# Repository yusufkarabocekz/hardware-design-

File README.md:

# Hardware Libraries Workspace

Bu repository, çeşitli donanım projeleri ve kütüphanelerini içeren kapsamlı bir workspace'tir. Endüstriyel sensör modülleri, güç yönetimi çözümleri, drone kontrolcüleri ve eğitim projeleri gibi farklı alanlarda geliştirilmiş projeleri barındırır.

## 📁 Proje Kategorileri

### 🔧 Endüstriyel Sensör Modülleri
- **Endüstriyel Sensör Modülü** - Endüstriyel uygulamalar için geliştirilmiş sensör modülü

- **UKB_Ballica** - UKB (Uçuş Kontrol Bilgisayarı) Sistemi

### ⚡ Güç Yönetimi Çözümleri
- **Güç Dağıtım Kartı** - Çoklu güç dağıtımı için tasarlanmış PCB

- **LM2596 Buck Converter** - Step-down (düşürücü) DC-DC dönüştürücü modülü

- **XL6009 Boost Converter** - Step-up (yükseltici) DC-DC dönüştürücü modülü

### 🚁 Drone ve Uçuş Kontrolcüleri
- **flight-controller-for-dronmarket-main** - Drone market için özel uçuş kontrolcüsü

- **speedybeef4v4_clone** - SpeedyBee F4 V4 uçuş kontrolcüsü klonu

### 📊 IMU ve Sensör Sürücüleri
- **STM32-ICM42688-P** - ICM-42688-P IMU sensörü için STM32 sürücüsü

- **stm32f103_bmi088** - BMI-088 IMU sensörü için STM32F103 sürücüsü

### 🎓 Eğitim Projeleri
- **xBowtie Eğitim** - xBowtie platformu - Mustafa Berk Aydoğan - PCB Tasarım - Bir Elektronik Kartın Yaşam Döngüsü

## 🚀 Özellikler

- **Modüler Tasarım**: Her proje bağımsız olarak geliştirilmiş ve kullanılabilir
- **Çoklu Platform Desteği**: STM32, Arduino ve diğer mikrodenetleyici platformları
- **Kapsamlı Dokümantasyon**: Her proje için detaylı README dosyaları
- **Örnek Kodlar**: Pratik kullanım için hazırlanmış örnekler
- **Endüstriyel Standartlar**: Profesyonel geliştirme standartlarına uygun

## 📋 Proje Listesi

| Proje Adı | Kategori | Açıklama |
|-----------|----------|----------|
| Endüstriyel Sensör Modülü | Endüstriyel | Endüstriyel uygulamalar için sensör modülü |
| UKB_Ballica | Endüstriyel | Ultrasonik kuvvet basınç sensörü |
| Güç Dağıtım Kartı | Güç Yönetimi | Çoklu güç dağıtım PCB'si |
| LM2596 Buck Converter | Güç Yönetimi | Step-down DC-DC dönüştürücü |
| XL6009 Boost Converter | Güç Yönetimi | Step-up DC-DC dönüştürücü |
| STM32-ICM42688-P | IMU/Sensör | ICM-42688-P STM32 sürücüsü |
| stm32f103_bmi088 | IMU/Sensör | BMI-088 STM32F103 sürücüsü |
| flight-controller-for-dronmarket-main | Drone | Drone market uçuş kontrolcüsü |
| speedybeef4v4_clone | Drone | SpeedyBee F4 V4 klonu |
| xBowtie Eğitim | Eğitim | xBowtie eğitim materyalleri |

## 🛠️ Teknolojiler

- **Mikrodenetleyiciler**: STM32F103, STM32F4, Arduino
- **Sensörler**: BMI-088, ICM-42688-P, MPU9250, GPS M8N, MS5611 etc. 
- **İletişim Protokolleri**: I2C, SPI, UART, RS232/485
- **PCB Tasarım**: KiCad
- **Programlama**: C, C++, Arduino, STM32
- **Güç Yönetimi**: LM2596, XL6009

## 🤝 Katkıda Bulunma

1. Bu repository'yi fork edin
2. Yeni bir branch oluşturun (`git checkout -b feature/yeni-ozellik`)
3. Değişikliklerinizi commit edin (`git commit -am 'Yeni özellik eklendi'`)
4. Branch'inizi push edin (`git push origin feature/yeni-ozellik`)
5. Pull Request oluşturun

## 📄 Lisans

Bu projeler açık kaynak olarak geliştirilmiştir. Her proje kendi lisans bilgilerini içerir.

## 📞 İletişim

Projeler hakkında sorularınız için:
- GitHub Issues kullanabilirsiniz

---

**Not**: Bu workspace sürekli güncellenmektedir. Yeni projeler ve güncellemeler için repository'yi takip etmeyi unutmayın.

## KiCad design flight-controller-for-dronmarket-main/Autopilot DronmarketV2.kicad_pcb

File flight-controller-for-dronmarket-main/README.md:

# flight-controller-for-dronmarket

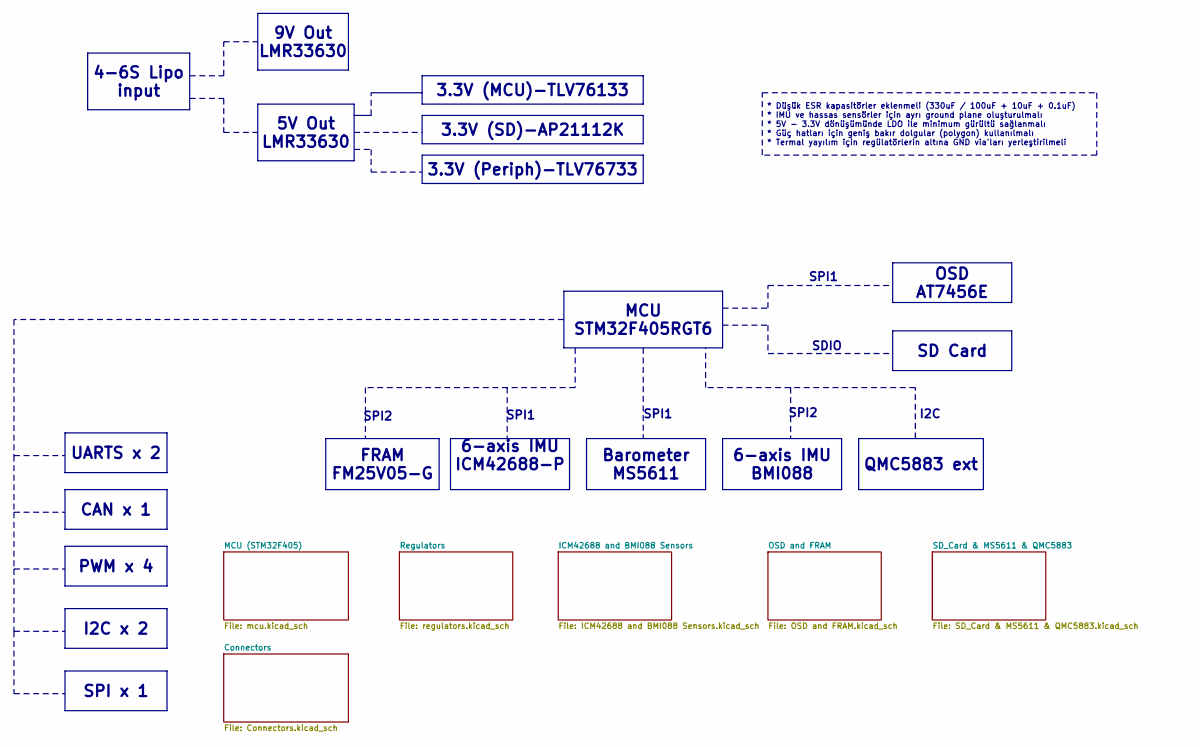
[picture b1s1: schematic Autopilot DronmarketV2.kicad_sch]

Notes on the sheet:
SDIO
SPI1
SPI1
I2C
SPI2
QMC5883 ext
6-axis IMU BMI088
I2C x 2
FRAM FM25V05-G
SD Card
3.3V (MCU)-TLV76133
6-axis IMU ICM42688-P
Barometer MS5611
3.3V (Periph)-TLV76733
4-6S Lipo input
5V Out LMR33630
SPI x 1
MCU STM32F405RGT6
PWM x 4
UARTS x 2
9V Out LMR33630
OSD AT7456E
3.3V (SD)-AP21112K
CAN x 1
* Düşük ESR kapasitörler eklenmeli (330uF / 100uF + 10uF + 0.1uF) * IMU ve hassas sensörler için ayrı ground plane oluşturulmalı * 5V - 3.3V dönüşümünde LDO ile minimum gürültü sağlanmalı * Güç hatları için geniş bakır dolgular (polygon) kullanılmalı * Termal yayılım için regülatörlerin altına GND 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

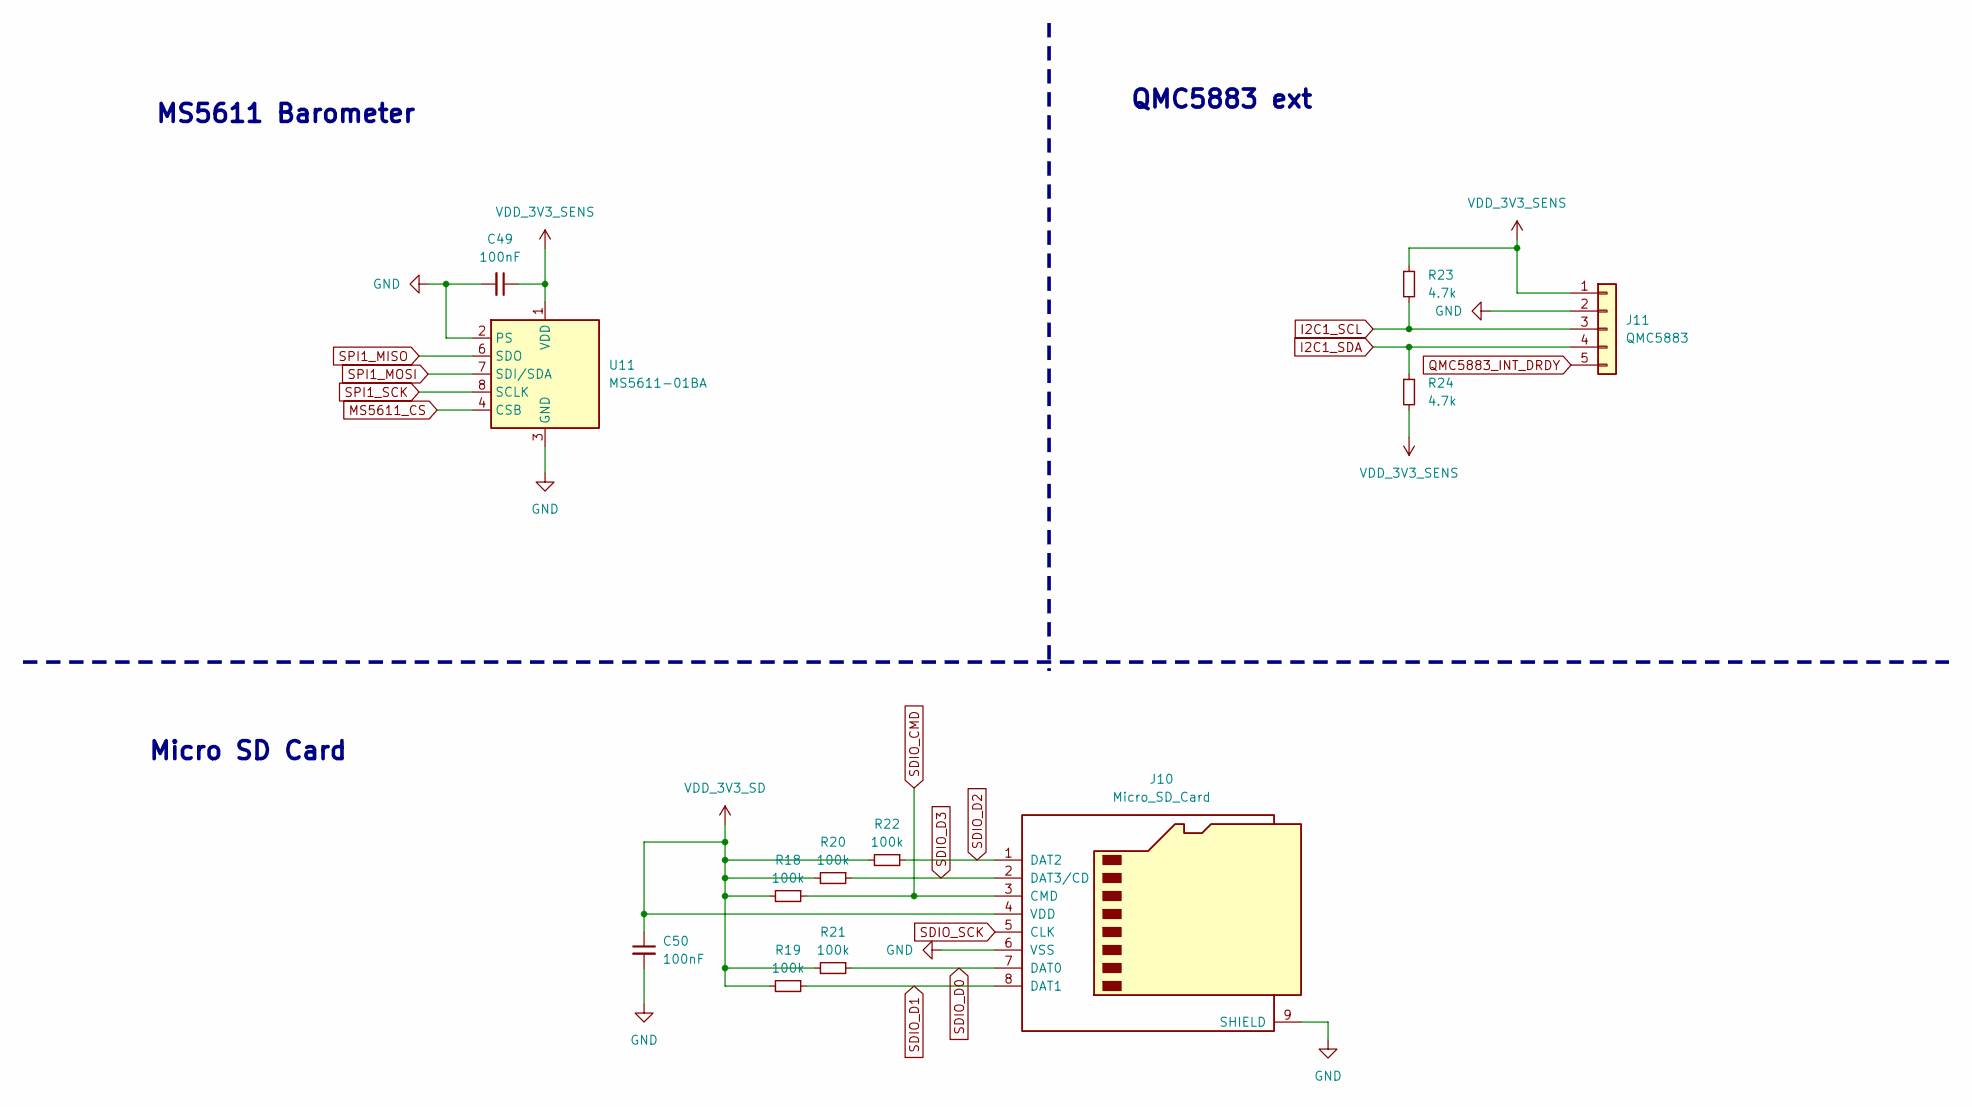
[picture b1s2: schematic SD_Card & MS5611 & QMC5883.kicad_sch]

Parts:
C49, C50: 100nF; C_0402_1005Metric
J10: Micro_SD_Card; MOLEX_503398-1892
J11: QMC5883; JST_GH_SM05B-GHS-TB_1x05-1MP_P1.25mm_Horizontal
R18, R19, R20, R21, R22: 100k; R_0402_1005Metric
R23, R24: 4.7k; R_0402_1005Metric
U11: MS5611-01BA; LGA-8_3x5mm_P1.25mm

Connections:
GND: C49.2, C50.2, J10.6 (VSS), J10.9 (SHIELD), J11.2, J11.MP, U11.2 (PS), U11.3 (GND); also elsewhere on the board
I2C1_SCL: J11.3, R23.2; also elsewhere on the board
I2C1_SDA: J11.4, R24.1; also elsewhere on the board
MS5611_CS: U11.4 (CSB), U11.5 (CSB); also elsewhere on the board
QMC5883_INT_DRDY: J11.5; also elsewhere on the board
SDIO_CMD: J10.3 (CMD), R18.1; also elsewhere on the board
SDIO_D0: J10.7 (DAT0), R21.1; also elsewhere on the board
SDIO_D1: J10.8 (DAT1), R19.1; also elsewhere on the board
SDIO_D2: J10.1 (DAT2), R22.1; also elsewhere on the board
SDIO_D3: J10.2 (DAT3/CD), R20.1; also elsewhere on the board
SDIO_SCK: J10.5 (CLK); also elsewhere on the board
SPI1_MISO: U11.6 (SDO); also elsewhere on the board
SPI1_MOSI: U11.7 (SDI/SDA); also elsewhere on the board
SPI1_SCK: U11.8 (SCLK); also elsewhere on the board
VDD_3V3_SD: C50.1, J10.4 (VDD), R18.2, R19.2, R20.2, R21.2, R22.2; also elsewhere on the board
VDD_3V3_SENS: C49.1, J11.1, R23.1, R24.2, U11.1 (VDD); also elsewhere on the board

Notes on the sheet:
QMC5883 ext
Micro SD Card
MS5611 Barometer

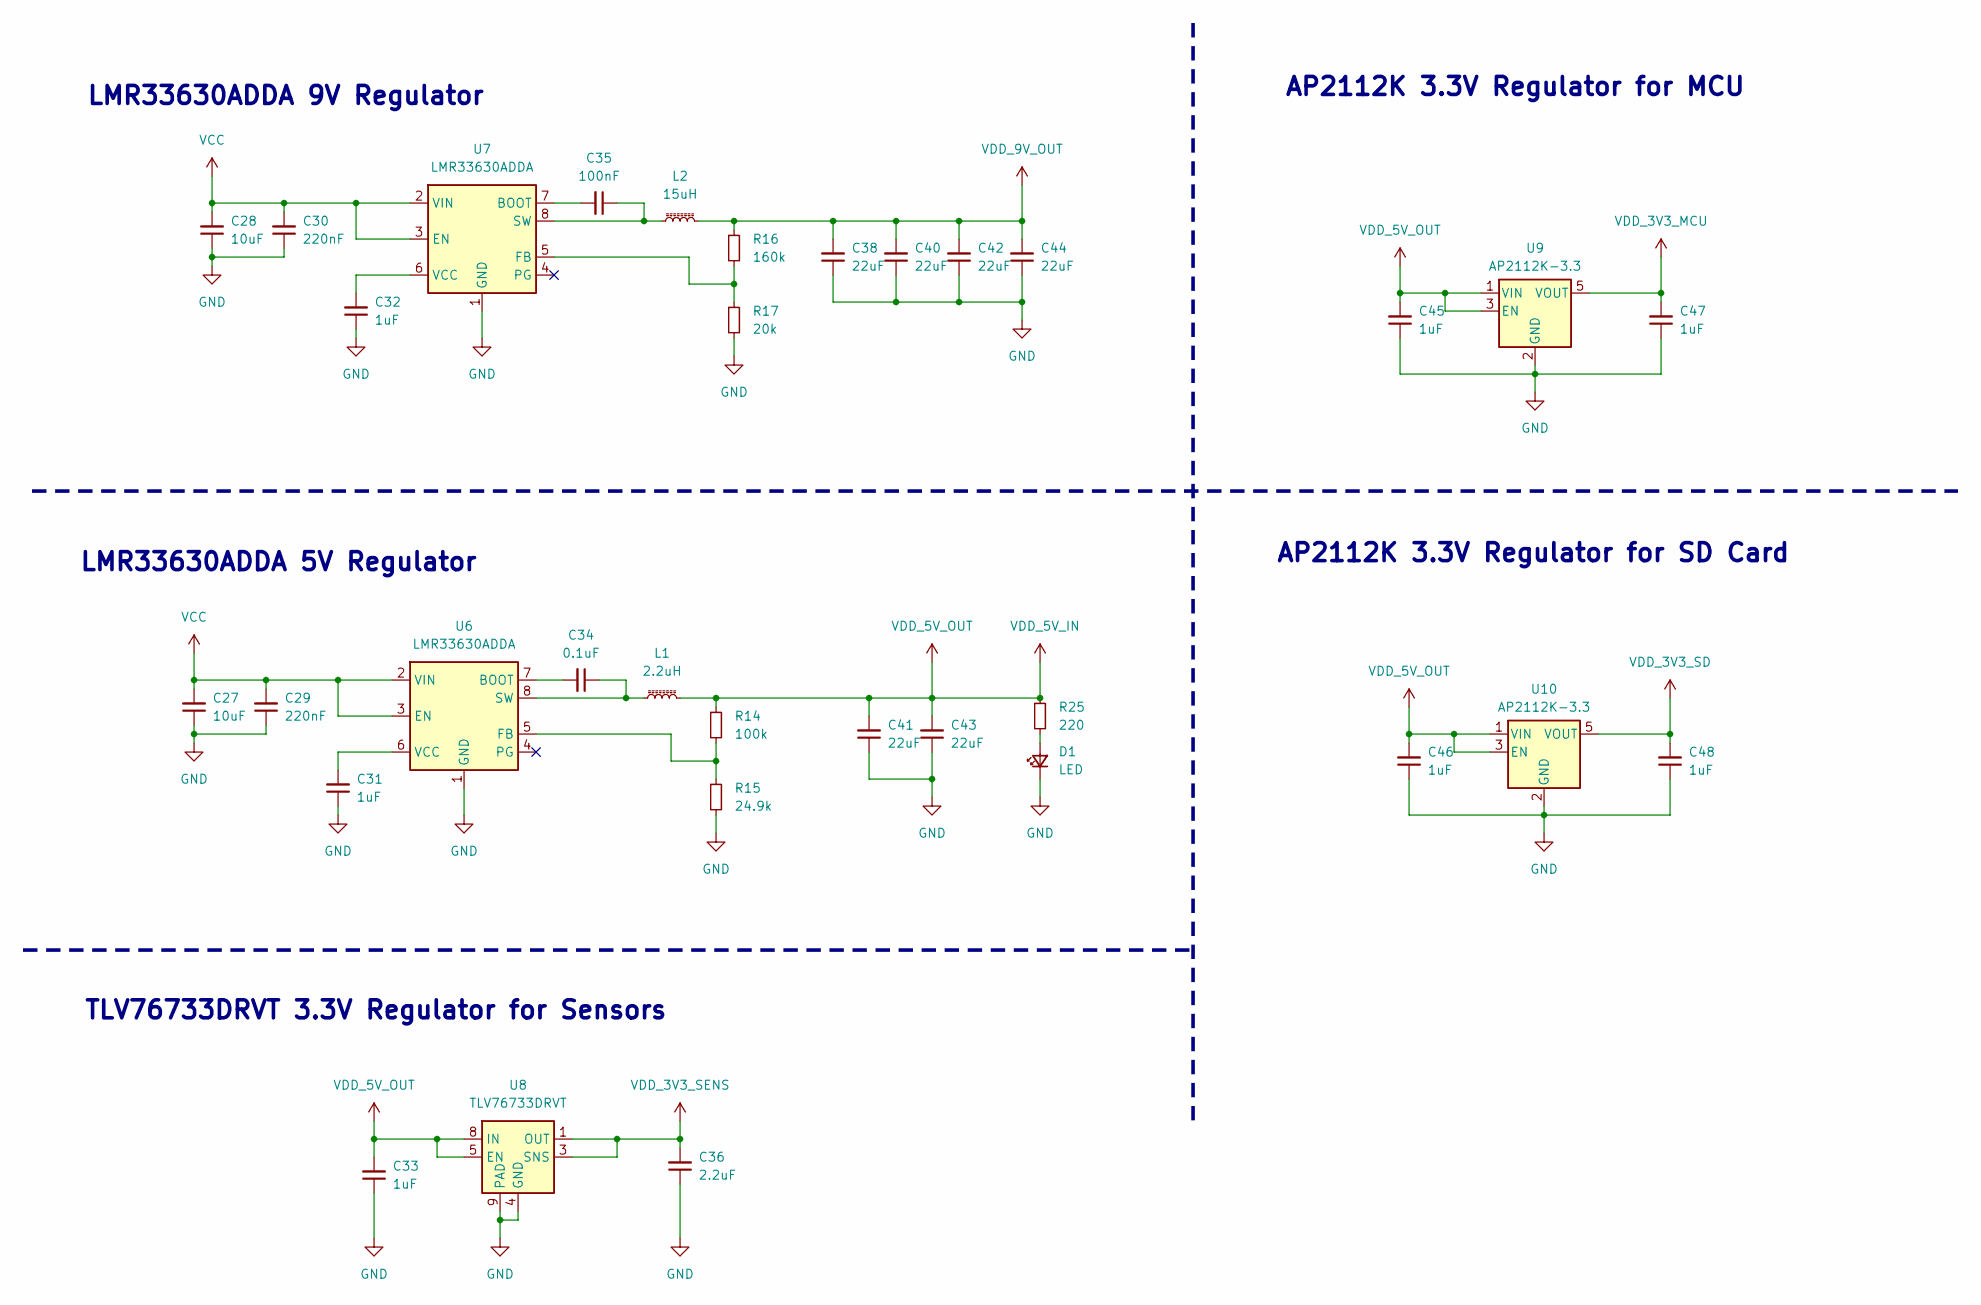
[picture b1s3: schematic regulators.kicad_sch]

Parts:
C27, C28: 10uF; C_0402_1005Metric
C29, C30: 220nF; C_0402_1005Metric
C31, C32, C33, C45, C46, C47, C48: 1uF; C_0402_1005Metric
C34: 0.1uF; C_0402_1005Metric
C35: 100nF; C_0402_1005Metric
C36: 2.2uF; C_0402_1005Metric
C38, C40, C41, C42, C43, C44: 22uF; C_0402_1005Metric
D1: LED; LED_0603_1608Metric
L1: 2.2uH; L_Chilisin_BMRB00060650
L2: 15uH; L_Chilisin_BMRB00060650
R14: 100k; R_0402_1005Metric
R15: 24.9k; R_0402_1005Metric
R16: 160k; R_0402_1005Metric
R17: 20k; R_0402_1005Metric
R25: 220; R_0402_1005Metric
U6, U7: LMR33630ADDA; Texas_HSOP-8-1EP_3.9x4.9mm_P1.27mm_ThermalVias
U8: TLV76733DRVT; SON65P200X200X80-7N
U9, U10: AP2112K-3.3; SOT-23-5

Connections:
GND: C27.1, C28.1, C29.1, C30.1, C31.1, C32.1, C33.1, C36.1, C38.1, C40.1, C41.1, C42.1, C43.1, C44.1, C45.1, C46.1, C47.1, C48.1, D1.1 (K), R15.2, R17.2, U6.1 (GND), U6.9 (GND), U7.1 (GND), U7.9 (GND), U8.4 (GND), U8.6 (GND), U8.9 (PAD), U9.2 (GND), U10.2 (GND); also elsewhere on the board
unnamed: D1.2 (A), R25.2
unnamed: C34.2, U6.7 (BOOT)
unnamed: R14.2, R15.1, U6.5 (FB)
unnamed: C34.1, L1.1, U6.8 (SW)
unnamed: C31.2, U6.6 (VCC)
unnamed: C35.2, U7.7 (BOOT)
unnamed: R16.2, R17.1, U7.5 (FB)
unnamed: C35.1, L2.1, U7.8 (SW)
unnamed: C32.2, U7.6 (VCC)
VCC: C27.2, C28.2, C29.2, C30.2, U6.2 (VIN), U6.3 (EN), U7.2 (VIN), U7.3 (EN); also elsewhere on the board
VDD_3V3_MCU: C47.2, U9.5 (VOUT); also elsewhere on the board
VDD_3V3_SD: C48.2, U10.5 (VOUT); also elsewhere on the board
VDD_3V3_SENS: C36.2, U8.1 (OUT), U8.3 (SNS); also elsewhere on the board
VDD_5V_IN: C33.2, C41.2, C43.2, C45.2, C46.2, L1.2, R14.1, R25.1, U8.5 (EN), U8.8 (IN), U9.1 (VIN), U9.3 (EN), U10.1 (VIN), U10.3 (EN); also elsewhere on the board
VDD_9V_OUT: C38.2, C40.2, C42.2, C44.2, L2.2, R16.1; also elsewhere on the board

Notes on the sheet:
TLV76733DRVT 3.3V Regulator for Sensors
AP2112K 3.3V Regulator for MCU
AP2112K 3.3V Regulator for SD Card
LMR33630ADDA 9V Regulator
LMR33630ADDA 5V Regulator

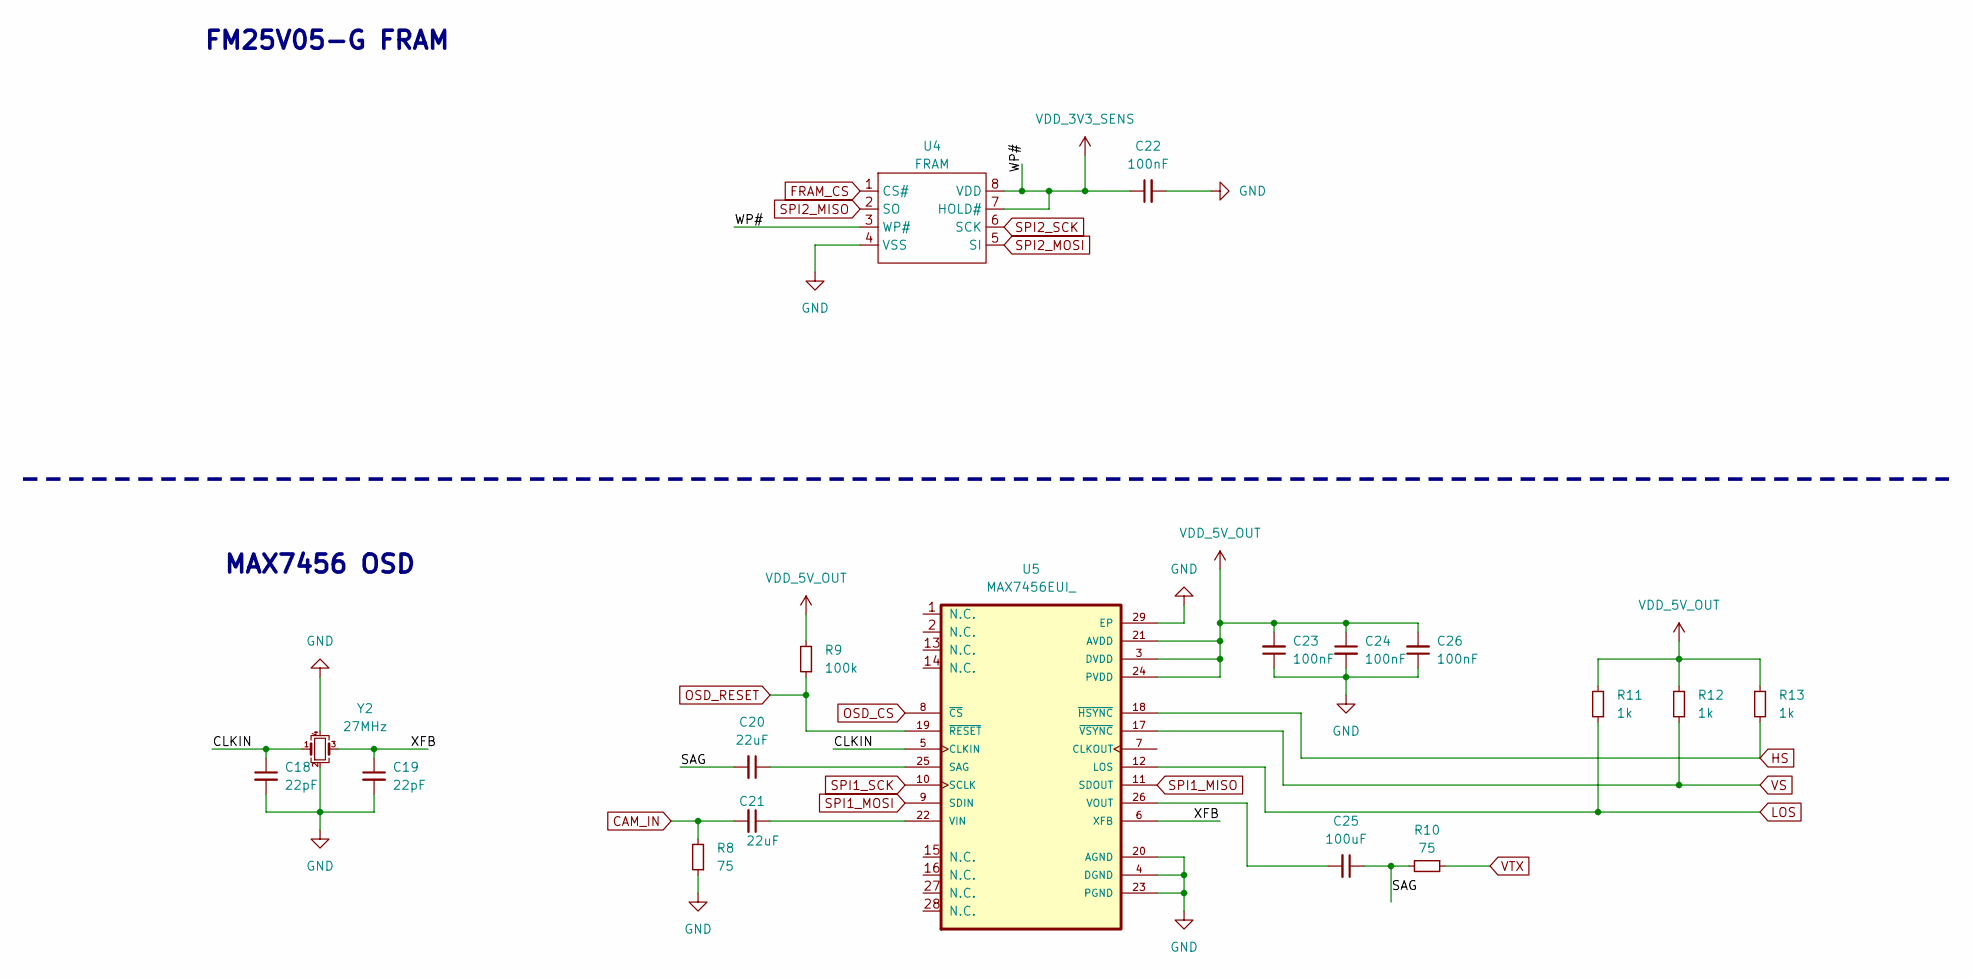
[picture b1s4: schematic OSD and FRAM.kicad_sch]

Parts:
C18, C19: 22pF; C_0402_1005Metric
C20: 22uF; C_0402_1005Metric
C21: 22uF; C_1210_3225Metric
C22, C23, C24, C26: 100nF; C_0402_1005Metric
C25: 100uF; C_1210_3225Metric
R8, R10: 75; R_0402_1005Metric
R9: 100k; R_0402_1005Metric
R11, R12, R13: 1k; R_0402_1005Metric
U4: FRAM; SOIC127P602X172-8N
U5: MAX7456EUI_; SOP65P637X110-28N
Y2: 27MHz; Crystal_SMD_SeikoEpson_FA238V-4Pin_3.2x2.5mm

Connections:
/OSD and FRAM/CLKIN: C18.1, U5.5 (CLKIN), Y2.1
/OSD and FRAM/SAG: C20.2, C25.1, R10.2
/OSD and FRAM/XFB: C19.1, U5.6 (XFB), Y2.3
CAM_IN: C21.2, R8.2; also elsewhere on the board
FRAM_CS: U4.1 (CS#); also elsewhere on the board
GND: C18.2, C19.2, C22.2, C23.1, C24.2, C26.1, R8.1, U4.4 (VSS), U5.4 (DGND), U5.20 (AGND), U5.23 (PGND), U5.29 (EP), Y2.2, Y2.4; also elsewhere on the board
HS: R13.2, U5.18 (~HSYNC)
LOS: R11.1, U5.12 (LOS)
unnamed: C20.1, U5.25 (SAG)
unnamed: C21.1, U5.22 (VIN)
unnamed: C25.2, U5.26 (VOUT)
OSD_CS: U5.8 (~CS); also elsewhere on the board
OSD_RESET: R9.1, U5.19 (~RESET)
SPI1_MISO: U5.11 (SDOUT); also elsewhere on the board
SPI1_MOSI: U5.9 (SDIN); also elsewhere on the board
SPI1_SCK: U5.10 (SCLK); also elsewhere on the board
SPI2_MISO: U4.2 (SO); also elsewhere on the board
SPI2_MOSI: U4.5 (SI); also elsewhere on the board
SPI2_SCK: U4.6 (SCK); also elsewhere on the board
VDD_3V3_SENS: C22.1, U4.3 (WP#), U4.7 (HOLD#), U4.8 (VDD); also elsewhere on the board
VDD_5V_IN: C23.2, C24.1, C26.2, R9.2, R11.2, R12.2, R13.1, U5.3 (DVDD), U5.21 (AVDD), U5.24 (PVDD); also elsewhere on the board
VS: R12.1, U5.17 (~VSYNC)
VTX: R10.1; also elsewhere on the board

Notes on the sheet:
MAX7456 OSD
FM25V05-G FRAM

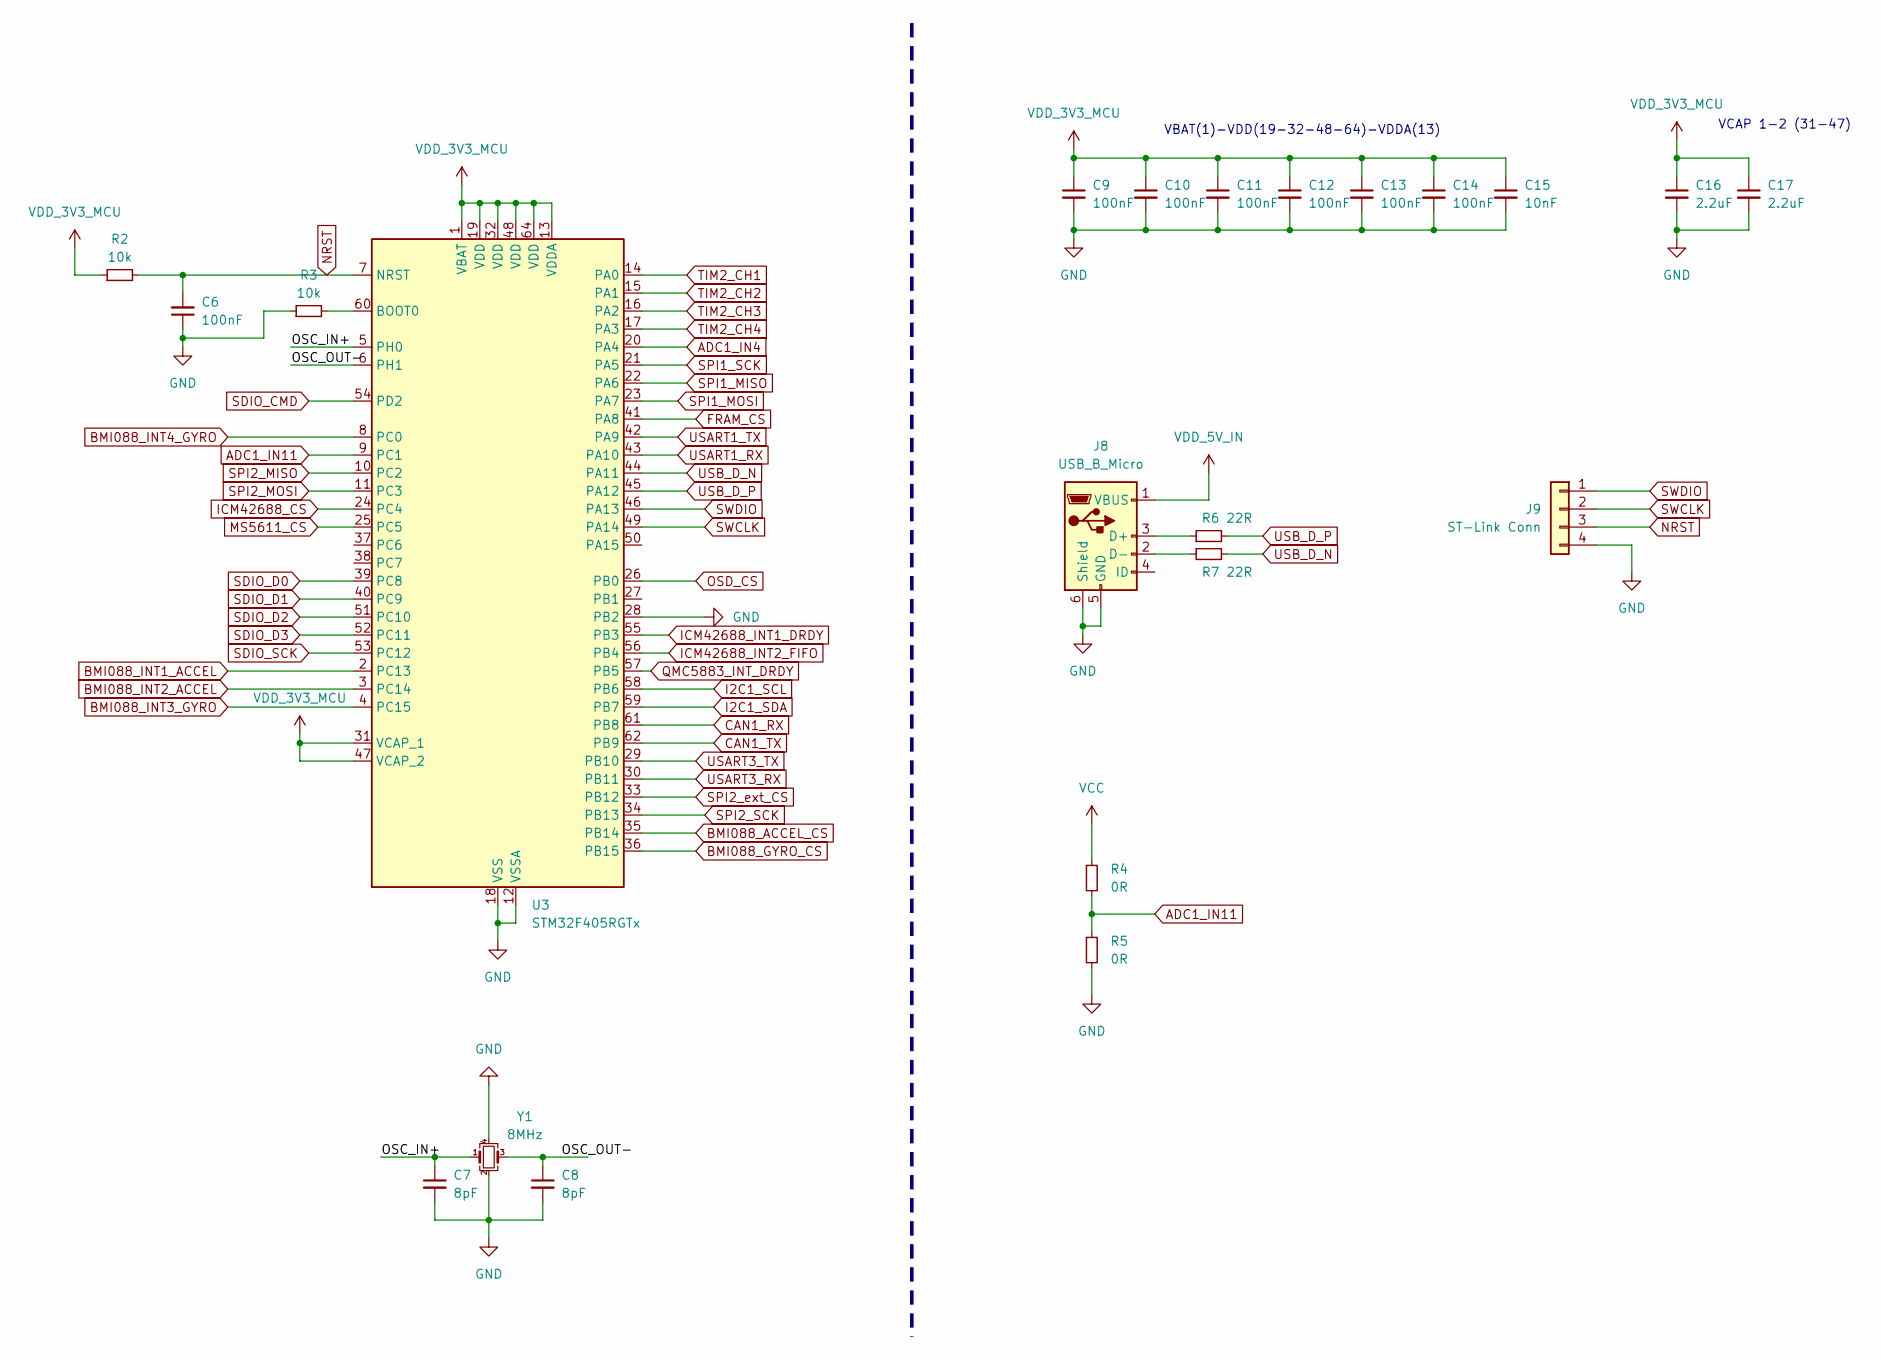
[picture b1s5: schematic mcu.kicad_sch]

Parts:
C6, C9, C10, C11, C12, C13, C14: 100nF; C_0402_1005Metric
C7, C8: 8pF; C_0402_1005Metric
C15: 10nF; C_0402_1005Metric
C16, C17: 2.2uF; C_0402_1005Metric
J8: USB_B_Micro; USB_Micro-B_Molex_47346-0001
J9: ST-Link Conn; JST_GH_SM04B-GHS-TB_1x04-1MP_P1.25mm_Horizontal
R2, R3: 10k; R_0402_1005Metric
R4, R5: 0R; R_0402_1005Metric
R6, R7: 22R; R_0402_1005Metric
U3: STM32F405RGTx; LQFP-64_10x10mm_P0.5mm
Y1: 8MHz; Crystal_SMD_SeikoEpson_FA238V-4Pin_3.2x2.5mm

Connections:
/MCU (STM32F405)/OSC_IN+: C7.1, U3.5 (PH0), Y1.1
/MCU (STM32F405)/OSC_OUT-: C8.1, U3.6 (PH1), Y1.3
ADC1_IN4: U3.20 (PA4); also elsewhere on the board
ADC1_IN11: R4.2, R5.1, U3.9 (PC1)
BMI088_ACCEL_CS: U3.35 (PB14); also elsewhere on the board
BMI088_GYRO_CS: U3.36 (PB15); also elsewhere on the board
BMI088_INT1_ACCEL: U3.2 (PC13); also elsewhere on the board
BMI088_INT2_ACCEL: U3.3 (PC14); also elsewhere on the board
BMI088_INT3_GYRO: U3.4 (PC15); also elsewhere on the board
BMI088_INT4_GYRO: U3.8 (PC0); also elsewhere on the board
CAN1_RX: U3.61 (PB8); also elsewhere on the board
CAN1_TX: U3.62 (PB9); also elsewhere on the board
FRAM_CS: U3.41 (PA8); also elsewhere on the board
GND: C6.1, C7.2, C8.2, C9.2, C10.2, C11.2, C12.2, C13.2, C14.2, C15.2, C16.2, C17.2, J8.5 (GND), J8.6 (Shield), J9.4, J9.MP, R3.1, R5.2, U3.12 (VSSA), U3.18 (VSS), U3.28 (PB2), U3.63 (VSS), Y1.2, Y1.4; also elsewhere on the board
I2C1_SCL: U3.58 (PB6); also elsewhere on the board
I2C1_SDA: U3.59 (PB7); also elsewhere on the board
ICM42688_CS: U3.24 (PC4); also elsewhere on the board
ICM42688_INT1_DRDY: U3.55 (PB3); also elsewhere on the board
ICM42688_INT2_FIFO: U3.56 (PB4); also elsewhere on the board
MS5611_CS: U3.25 (PC5); also elsewhere on the board
NRST: C6.2, J9.3, R2.2, U3.7 (NRST)
unnamed: J8.3 (D+), R6.1
unnamed: J8.2 (D-), R7.1
unnamed: R3.2, U3.60 (BOOT0)
OSD_CS: U3.26 (PB0); also elsewhere on the board
QMC5883_INT_DRDY: U3.57 (PB5); also elsewhere on the board
SDIO_CMD: U3.54 (PD2); also elsewhere on the board
SDIO_D0: U3.39 (PC8); also elsewhere on the board
SDIO_D1: U3.40 (PC9); also elsewhere on the board
SDIO_D2: U3.51 (PC10); also elsewhere on the board
SDIO_D3: U3.52 (PC11); also elsewhere on the board
SDIO_SCK: U3.53 (PC12); also elsewhere on the board
SPI1_MISO: U3.22 (PA6); also elsewhere on the board
SPI1_MOSI: U3.23 (PA7); also elsewhere on the board
SPI1_SCK: U3.21 (PA5); also elsewhere on the board
SPI2_MISO: U3.10 (PC2); also elsewhere on the board
SPI2_MOSI: U3.11 (PC3); also elsewhere on the board
SPI2_SCK: U3.34 (PB13); also elsewhere on the board
SPI2_ext_CS: U3.33 (PB12); also elsewhere on the board
SWCLK: J9.2, U3.49 (PA14)
SWDIO: J9.1, U3.46 (PA13)
TIM2_CH1: U3.14 (PA0); also elsewhere on the board
TIM2_CH2: U3.15 (PA1); also elsewhere on the board
TIM2_CH3: U3.16 (PA2); also elsewhere on the board
TIM2_CH4: U3.17 (PA3); also elsewhere on the board
USART1_RX: U3.43 (PA10); also elsewhere on the board
USART1_TX: U3.42 (PA9); also elsewhere on the board
USART3_RX: U3.30 (PB11); also elsewhere on the board
USART3_TX: U3.29 (PB10); also elsewhere on the board
USB_D_N: R7.2, U3.44 (PA11)
USB_D_P: R6.2, U3.45 (PA12)
VCC: R4.1; also elsewhere on the board
VDD_3V3_MCU: C9.1, C10.1, C11.1, C12.1, C13.1, C14.1, C15.1, C16.1, C17.1, R2.1, U3.1 (VBAT), U3.13 (VDDA), U3.19 (VDD), U3.31 (VCAP_1), U3.32 (VDD), U3.47 (VCAP_2), U3.48 (VDD), U3.64 (VDD); also elsewhere on the board
VDD_5V_IN: J8.1 (VBUS); also elsewhere on the board

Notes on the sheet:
VCAP 1-2 (31-47)
VBAT(1)-VDD(19-32-48-64)-VDDA(13)

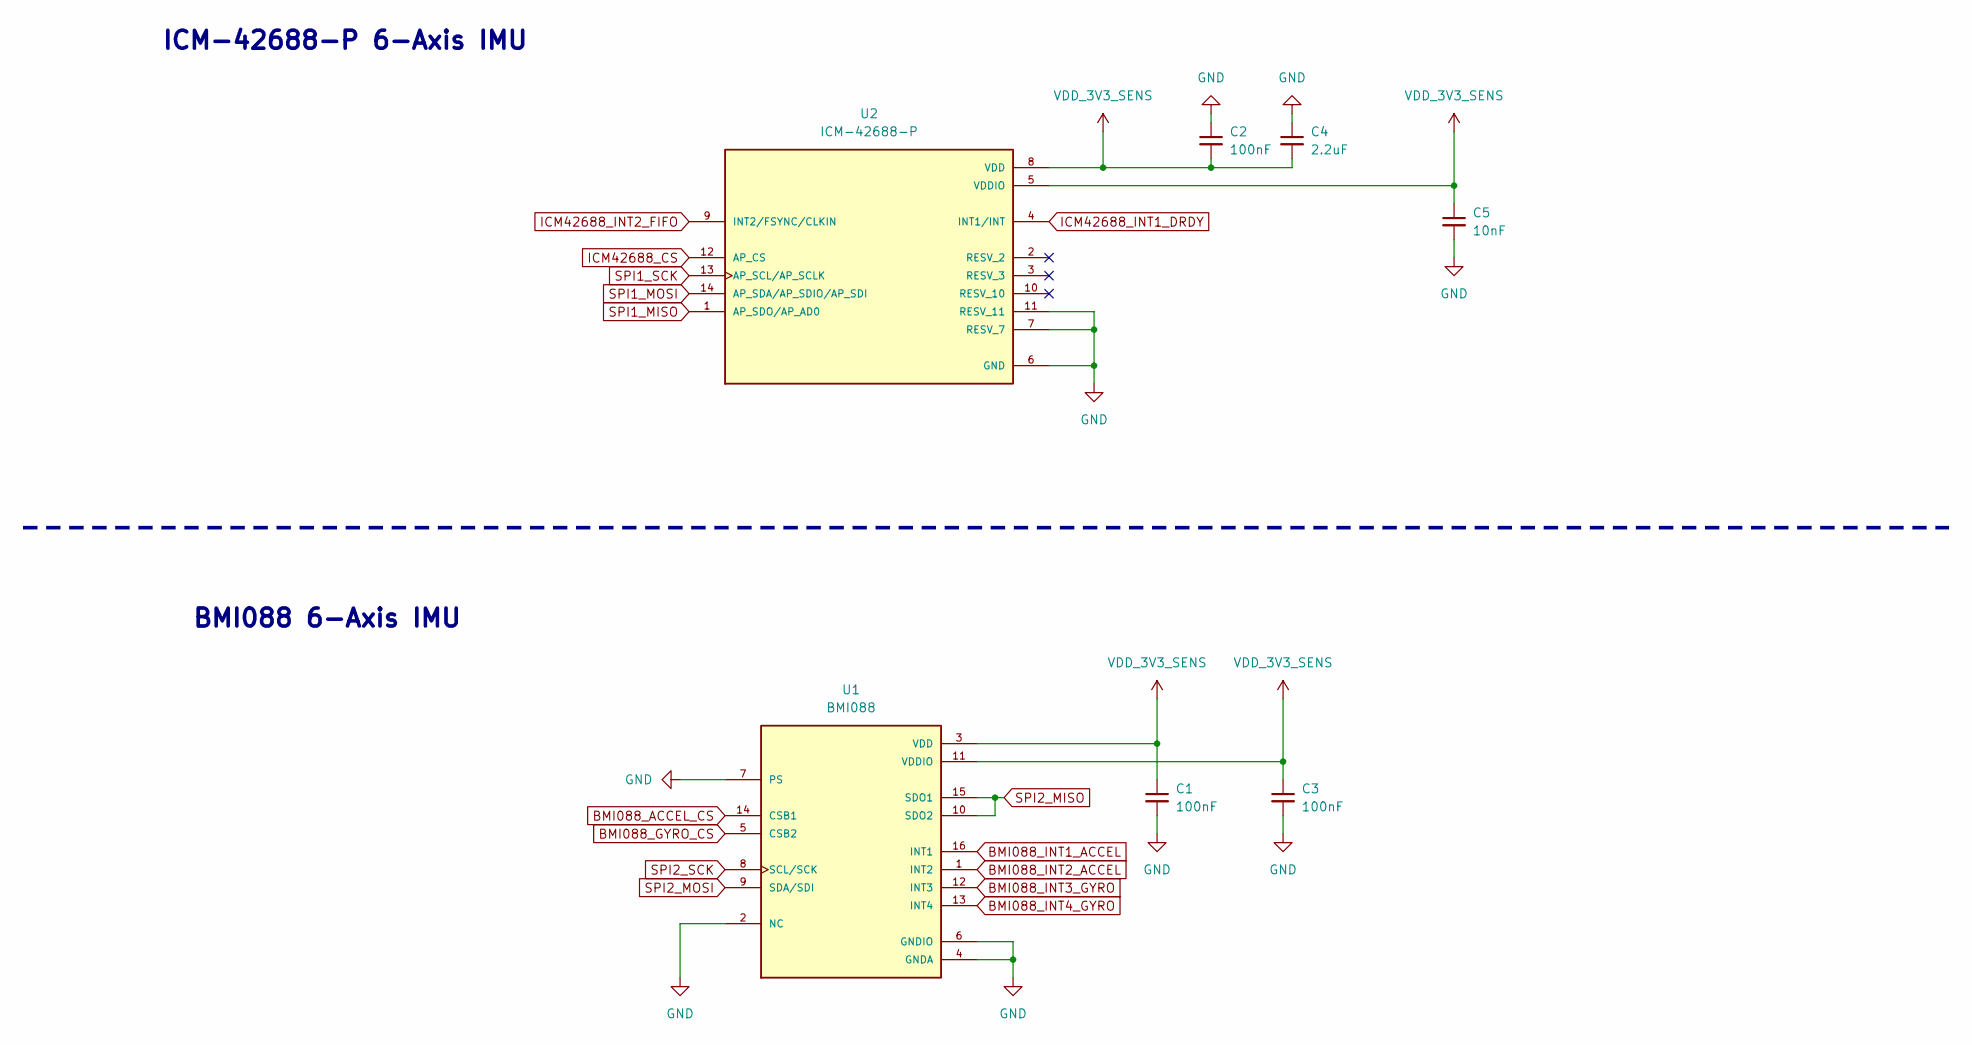
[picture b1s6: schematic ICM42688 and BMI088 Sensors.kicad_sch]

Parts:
C1, C2, C3: 100nF; C_0402_1005Metric
C4: 2.2uF; C_0402_1005Metric
C5: 10nF; C_0402_1005Metric
U1: BMI088; PQFN50P450X300X100-16N
U2: ICM-42688-P; PQFN50P300X250X97-14N; PARTREV 1.2

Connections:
BMI088_ACCEL_CS: U1.14 (CSB1); also elsewhere on the board
BMI088_GYRO_CS: U1.5 (CSB2); also elsewhere on the board
BMI088_INT1_ACCEL: U1.16 (INT1); also elsewhere on the board
BMI088_INT2_ACCEL: U1.1 (INT2); also elsewhere on the board
BMI088_INT3_GYRO: U1.12 (INT3); also elsewhere on the board
BMI088_INT4_GYRO: U1.13 (INT4); also elsewhere on the board
GND: C1.2, C2.1, C3.2, C4.1, C5.2, U1.2 (NC), U1.4 (GNDA), U1.6 (GNDIO), U1.7 (PS), U2.6 (GND), U2.7 (RESV_7), U2.11 (RESV_11); also elsewhere on the board
ICM42688_CS: U2.12 (AP_CS); also elsewhere on the board
ICM42688_INT1_DRDY: U2.4 (INT1/INT); also elsewhere on the board
ICM42688_INT2_FIFO: U2.9 (INT2/FSYNC/CLKIN); also elsewhere on the board
SPI1_MISO: U2.1 (AP_SDO/AP_AD0); also elsewhere on the board
SPI1_MOSI: U2.14 (AP_SDA/AP_SDIO/AP_SDI); also elsewhere on the board
SPI1_SCK: U2.13 (AP_SCL/AP_SCLK); also elsewhere on the board
SPI2_MISO: U1.10 (SDO2), U1.15 (SDO1); also elsewhere on the board
SPI2_MOSI: U1.9 (SDA/SDI); also elsewhere on the board
SPI2_SCK: U1.8 (SCL/SCK); also elsewhere on the board
VDD_3V3_SENS: C1.1, C2.2, C3.1, C4.2, C5.1, U1.3 (VDD), U1.11 (VDDIO), U2.5 (VDDIO), U2.8 (VDD); also elsewhere on the board

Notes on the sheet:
BMI088 6-Axis IMU
ICM-42688-P 6-Axis IMU

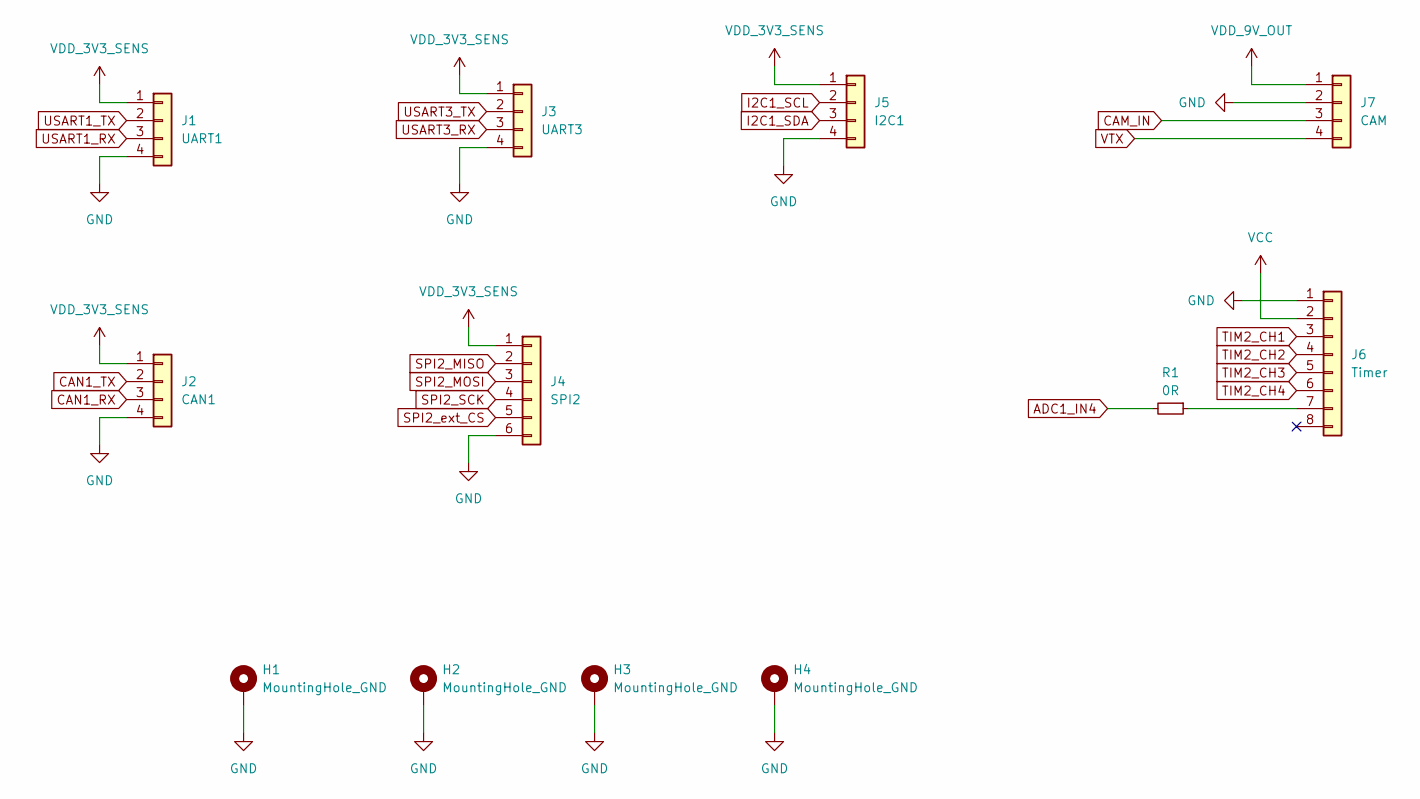
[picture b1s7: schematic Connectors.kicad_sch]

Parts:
H1, H2, H3, H4: MountingHole_GND; MountingHole_3.2mm_M3_Pad_Via
J1: UART1; JST_GH_SM04B-GHS-TB_1x04-1MP_P1.25mm_Horizontal
J2: CAN1; JST_GH_SM04B-GHS-TB_1x04-1MP_P1.25mm_Horizontal
J3: UART3; JST_GH_SM04B-GHS-TB_1x04-1MP_P1.25mm_Horizontal
J4: SPI2; JST_GH_SM06B-GHS-TB_1x06-1MP_P1.25mm_Horizontal
J5: I2C1; JST_GH_SM04B-GHS-TB_1x04-1MP_P1.25mm_Horizontal
J6: Timer; JST_GH_SM08B-GHS-TB_1x08-1MP_P1.25mm_Horizontal
J7: CAM; JST_GH_SM04B-GHS-TB_1x04-1MP_P1.25mm_Horizontal
R1: 0R; R_0402_1005Metric

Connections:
ADC1_IN4: R1.2; also elsewhere on the board
CAM_IN: J7.3; also elsewhere on the board
CAN1_RX: J2.3; also elsewhere on the board
CAN1_TX: J2.2; also elsewhere on the board
GND: H1.1, H2.1, H3.1, H4.1, J1.4, J1.MP, J2.4, J2.MP, J3.4, J3.MP, J4.6, J4.MP, J5.4, J5.MP, J6.1, J6.MP, J7.2, J7.MP; also elsewhere on the board
I2C1_SCL: J5.2; also elsewhere on the board
I2C1_SDA: J5.3; also elsewhere on the board
unnamed: J6.7, R1.1
SPI2_MISO: J4.2; also elsewhere on the board
SPI2_MOSI: J4.3; also elsewhere on the board
SPI2_SCK: J4.4; also elsewhere on the board
SPI2_ext_CS: J4.5; also elsewhere on the board
TIM2_CH1: J6.3; also elsewhere on the board
TIM2_CH2: J6.4; also elsewhere on the board
TIM2_CH3: J6.5; also elsewhere on the board
TIM2_CH4: J6.6; also elsewhere on the board
USART1_RX: J1.3; also elsewhere on the board
USART1_TX: J1.2; also elsewhere on the board
USART3_RX: J3.3; also elsewhere on the board
USART3_TX: J3.2; also elsewhere on the board
VCC: J6.2; also elsewhere on the board
VDD_3V3_SENS: J1.1, J2.1, J3.1, J4.1, J5.1; also elsewhere on the board
VDD_9V_OUT: J7.1; also elsewhere on the board
VTX: J7.4; also elsewhere on the board
